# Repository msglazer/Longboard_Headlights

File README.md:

# Longboard_Headlights
Headlights and Taillights for Longboard project

### Wired Headlight/Tail-light Module:

2X White/Red 1W LED's powered by E-board battery pack
12S(50.4V) Tolerant

### Battery Headlight/Tail-light Module:

2X White/Red 1W LED's powered by an 18650
3+ Hour battery life

#### Common features and Other Info:
Wired version is capable of dimming control through microcontroller, should also be able to make it flash this way as well
Both designs will be mounted through a truck riser. Wired version uses a 1/2" riser.

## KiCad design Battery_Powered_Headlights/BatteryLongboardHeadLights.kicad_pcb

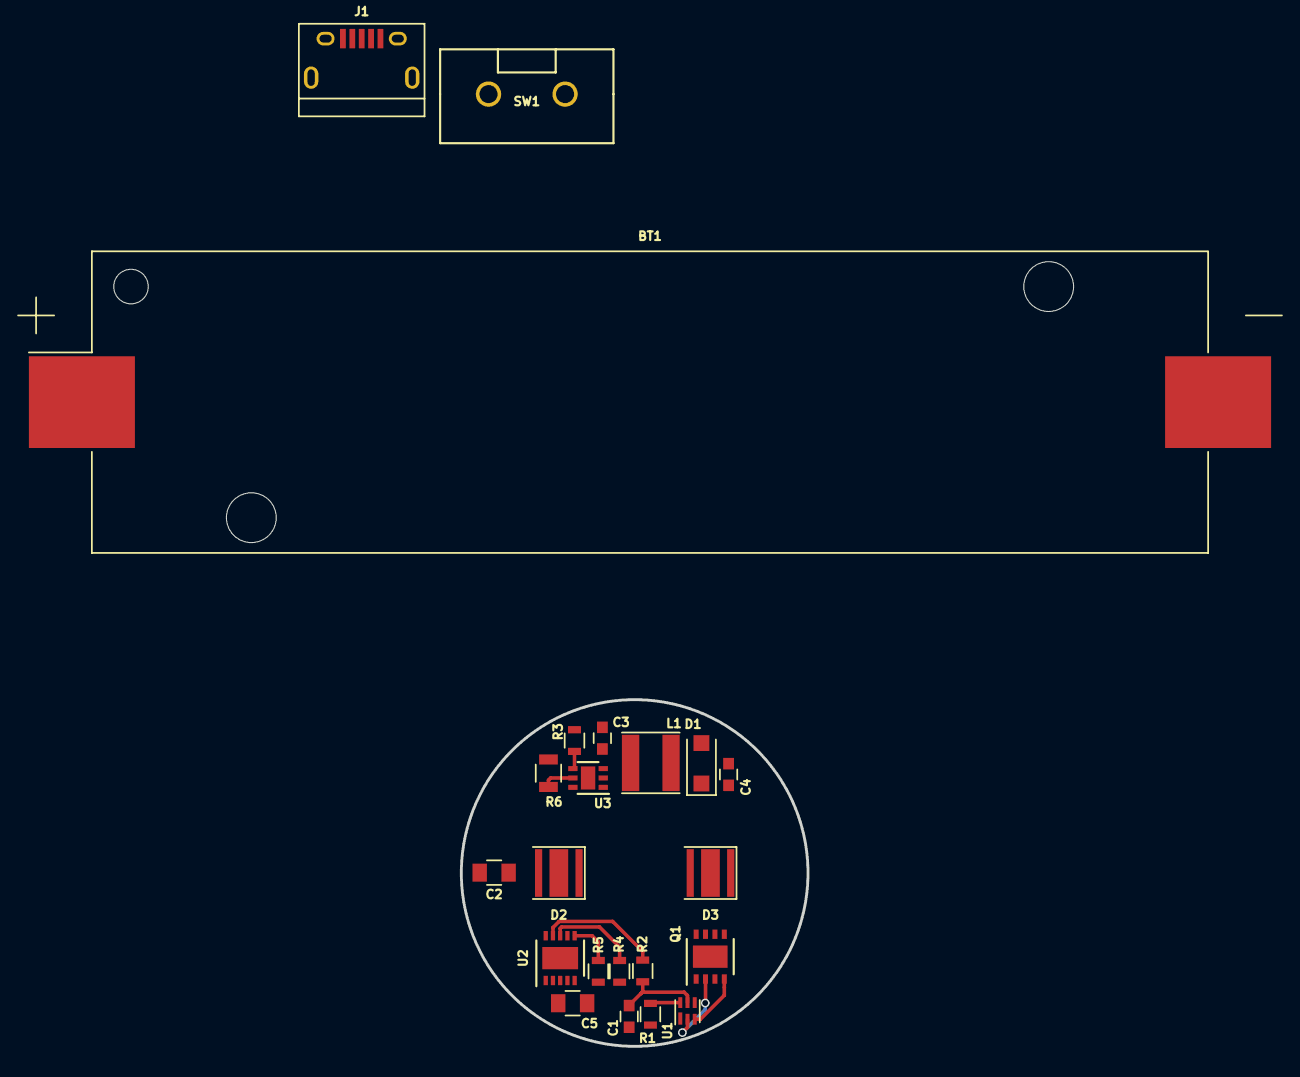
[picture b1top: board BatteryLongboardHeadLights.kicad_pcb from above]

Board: 2 copper layers, 24.0 x 24.0 mm, 22 parts (0 on the bottom side), 15 nets.

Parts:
BT1: Battery_Cell; Keystone_1042_1x18650
C1: 0.1uF; C_0603
C2, C5: 4.7uF; C_0805
C3: 4.7uF; C_0603
C4: 10uF; C_0603
D1: D_Schottky; D_SOD-123F
D2, D3: LED; LED_Cree-XP-G
J1: USB_OTG; USB_Micro-B
L1: 22uH; L_Taiyo-Yuden_NR-40xx
Q1: DMN2028UFDH-7; DFN-8-1EP_3x3mm_Pitch0.65mm
R1: 2.2K; R_0603
R2: 330; R_0603
R3: 10K; R_0603
R4: 20K; R_0603
R5: 1K; R_0603
R6: 0.3; R_0805
SW1: SW_Push; GPTS203212B
U1: bq29700; WSON6_1.5x1.5mm_Pitch0.5mm
U2: MCP73833T; DFN-10-1EP_3x3mm_Pitch0.5mm
U3: AP5724; DFN-6-1EP_2x2mm_Pitch0.65mm

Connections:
+BATT: BT1.1, C2.1, C3.1, L1.1, R2.1, SW1.1, U2.9, U2.10, U3.2
/SWITCH: R3.1, SW1.2, U3.4
/USB_IN: C5.1, J1.1, U2.1, U2.2
/VBAT_NEG: BT1.2, C1.2, Q1.3, R1.2, U1.4
GND: C2.2, C3.2, C4.2, C5.2, J1.5, J1.6, Q1.1, R3.2, R4.2, R5.2, R6.2, U2.5, U3.6
unnamed: C1.1, R2.2, U1.5
unnamed: C4.1, D1.1, D2.2, U3.3
unnamed: D1.2, L1.2, U3.1
unnamed: D2.1, D3.2
unnamed: D3.1, R6.1, U3.5
unnamed: Q1.2, U1.2
unnamed: Q1.4, U1.3
unnamed: R1.1, U1.6
unnamed: R4.1, U2.8
unnamed: R5.1, U2.6

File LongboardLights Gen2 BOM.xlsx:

Bill of Materials (BOM) - LongboardLights
 |  |  | Green - Forward Lighting, Blue - Rear Lighting, Orange - PCB
Item # | Board Qty | Prod. Qty | Ref Des | Manufacturer | Mfg Part # | Dist. Part # | Price Per Unit | Total Price | Description | Package | Type | Datasheet
1 | 1 | 1 | U1 | Texas Instruments | BQ29700DSER | 296-43985-1-ND | 0.69 | 0.69 | Battery Protection IC | 6-WFDFN | SMD | http://www.ti.com/lit/ds/symlink/bq2971.pdf
3 | 1 | 1 | U2 | Microchip Technology | MCP73833T-FCI/MF | MCP73833T-FCI/MFCT-ND | 0.89 | 0.89 | Battery Charger IC | 10-DFN | SMD | http://www.microchip.com/mymicrochip/filehandler.aspx?ddocna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
4 | 1 | 1 | U3 | Diodes Inc | AP5724FDCG-7 | AP5724FDCGDICT-ND | 0.45 | 0.45 | LED Driver IC | 16-WFQFN | SMD | http://www.ti.com/lit/ds/symlink/tps55330.pdf
5 | 1 | 1 | Q1 | Diodes Inc | DMN2040LTS-13 | DMN2040LTS-13DICT-ND | 0.46 | 0.46 | Dual NMOS common drain | 8-TSSOP | SMD | https://www.diodes.com/assets/Datasheets/ds31941.pdf
6 | 2 | 2 | D2,D3 | Cree Inc | XPGDWT-B1-0000-00LE1 | XPGDWT-B1-0000-00LE1CT-ND | 1.1399999999999999 | 2.2799999999999998 | 6500K White LED | 1414 | SMD | http://www.cree.com/led-components/media/documents/dsXPG3.pdf
6 | 2 | 2 | D2,D3 | Cree Inc | XPCRED-L1-R250-00201CT-ND | 941-XPCREDL1R250201 | 1.22 | 2.44 | Red LED | SMD-2 | SMD
7 | 1 | 1 | D1 | Diodes Inc | SS24FL | SS24FLCT-ND | 0.39 | 0.39 | Schottky Diode | SOD-123F | SMD | https://www.fairchildsemi.com/datasheets/SS/SS24FL.pdf
8 | 1 | 1 | C1 | Samsung | CL10B104KO8NNNC | 1276-1005-1-ND | 0.1 | 0.1 | 0.1uF Capacitor | 0603 | SMD
9 | 2 | 2 | C2,C3 | Samsung | CL10A475KO8NNNC | 1276-1784-1-ND | 0.26 | 0.52 | 4.7uF Capacitor | 0603 | SMD
11 | 1 | 1 | C4 | Samsung | CL21A106KOQNNNG | 1276-6455-1-ND | 0.13 | 0.13 | 10uF Capacitor | 0805 | SMD
15 | 1 | 1 | R6 | Samsung | RUT1608FR300CS | 1276-6168-1-ND | 0.17 | 0.17 | 0.3 ohm Resistor | 0603 | SMD
17 | 3 | 1 | R3 | Yageo | RC0603FR-0710KL | 311-10.0KHRCT-ND | 0.1 | 0.1 | 10k ohm resistor | 0603 | SMD
18 | 1 | 1 | R1 | Yageo | RC0603JR-072K2L | 311-2.2KGRCT-ND | 0.1 | 0.1 | 2.2K Ohm Resistor | 0603 | SMD
19 | 1 | 1 | R2 | Yageo | RC0603JR-07330RL | 311-330GRCT-ND | 0.1 | 0.1 | 330 Ohm Resistor | 0603 | SMD
22 | 1 | 1 | R4 | Yageo | RC0603JR-0720KL | 311-20KGRCT-ND | 0.1 | 0.1 | 20K Ohm Resistor | 0603 | SMD
23 | 1 | 1 | R5 | Yageo | RC0603FR-071KL | 311-1.00KHRCT-ND | 0.1 | 0.1 | 1K Ohm Resistor | 0603 | SMD
25 | 1 | 1 | L1 | Taiyo Yuden | NRS4018T220MDGJ | 587-2889-1-ND | 0.28999999999999998 | 0.28999999999999998 | 22uH Inductor | 6mm x 6mm | SMD
27 | 1 | 1 | B1 | Keystone Electronics | 1043 | 36-1043-ND | 2.31 | 2.31 | Battery Holder |  | ThruHole
28 | 1 | 1 | SW1 | CW Industries | GPTS203212B | CW182-ND | 0.74 | 0.74 | Power Button |  | ThruHole
29 | 1 | 1 | J1 | Amphenol | 10118194-0001LF | 609-4618-1-ND | 0.46 | 0.46 | Micro USB Port
30 | 1 | 1 | PCB | Oshpark | LR8zDDeL |  | 5 | 5 | PCB
 |  |  |  |  |  | Board Multiplier: | 1 | Headlight Total:
 |  |  |  |  |  |  |  | 10.379999999999999
 |  |  |  |  |  |  |  | Taillight Total:
 |  |  |  |  |  |  |  | 10.54
 |  |  |  |  |  |  |  | PCB Total:
 |  |  |  |  |  |  |  | 5
 |  |  |  |  |  |  |  | Grand Total:
 |  |  |  |  |  |  |  | 30.919999999999998

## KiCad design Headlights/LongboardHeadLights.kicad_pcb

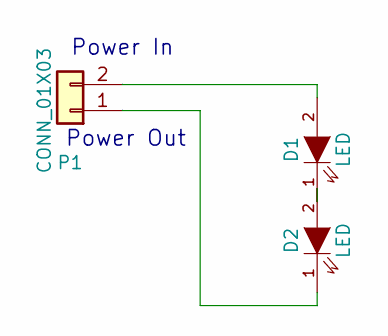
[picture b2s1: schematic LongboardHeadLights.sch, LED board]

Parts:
D1, D2: LED; LED-XP-G_CREE
P1: CONN_01X03; JST_EH_B02B-EH-A_02x2.50mm_Straight

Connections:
GND: D1.3, D2.3
unnamed: D1.1 (K), D2.2 (A)
unnamed: D1.2 (A), P1.2
unnamed: D2.1 (K), P1.1

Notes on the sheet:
Power In
Power Out

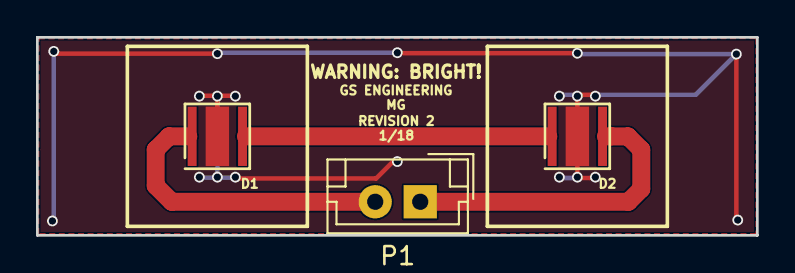
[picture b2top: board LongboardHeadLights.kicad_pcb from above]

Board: 2 copper layers, 40.0 x 11.0 mm, 3 parts (0 on the bottom side), 4 nets.

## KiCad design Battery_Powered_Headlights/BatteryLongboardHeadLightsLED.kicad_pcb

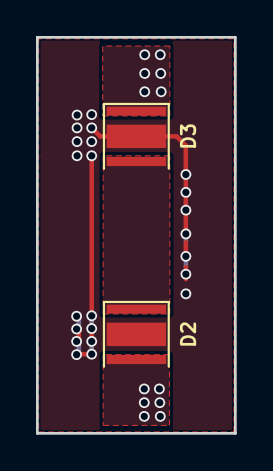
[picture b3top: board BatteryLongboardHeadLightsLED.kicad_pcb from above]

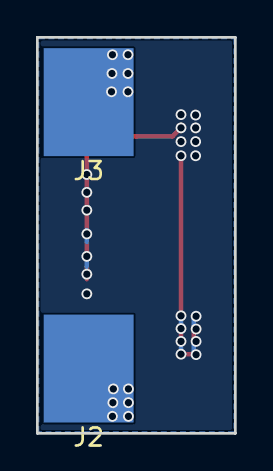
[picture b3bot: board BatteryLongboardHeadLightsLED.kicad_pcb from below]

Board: 2 copper layers, 11.0 x 22.0 mm, 4 parts (2 on the bottom side), 4 nets.

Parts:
D2, D3: LED; LED_Cree-XP-G
J2, J3: Conn_01x01; SolderWirePad_single_SMD_5x6mm

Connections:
GND: D2.3, D3.3
unnamed: D2.2, J2.1
unnamed: D2.1, D3.2
unnamed: D3.1, J3.1

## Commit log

2016-09-27 :circus_tent: Added .gitattributes & .gitignore files
2016-10-01 initial schematic build out
2016-10-14 PCB work
2016-10-14 small schematic changes
2016-10-14 updated BOM
2016-11-16 Generated Gerbers
2016-11-16 updated project and completed rev 1 PCB
2017-02-11 finished PCB, updating plan
    ditched tail light turn signal idea, now only need one PCB and just
    switch out LEDs
2017-02-11 couple quick changes
2017-02-11 fixed a bad trace
2017-02-11 yet another fix
2017-02-12 another small tweak
2017-02-12 added a PCB image
2017-02-12 fixed BOM
2017-10-31 redesigning the headlights to be battery powered
2017-11-01 schematic changes nearly done
2017-11-01 updating BOM
2017-11-02 Schematic done, values almost, layout next
2017-11-02 BOM update
2017-11-06 schematic completed
2017-11-06 BOM completed
2017-11-12 PCB work in progress
2017-11-19 PCB layout for the Batteryboard/LEDcontroller done
2017-11-27 PCB's should now be orderable
2018-01-23 updating designs for newest revision; removing unneeded files
2018-01-23 added design PDF
2018-01-23 bulk of power electronics schematic done
2018-01-23 updating readme since project has changed a lot
2018-01-24 schematic done, adding footprints
